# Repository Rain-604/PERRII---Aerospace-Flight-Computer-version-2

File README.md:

# PERRII – Aerospace Flight Computer version 2

## Project Overview
PERRII is a modular aerospace flight computer designed for environmental sensing and long-range data telemetry. The system is built around the ESP32-S3 Zero microcontroller and is designed to function as a scientific payload for high-altitude ballooning or atmospheric research. It integrates precision GNSS positioning, environmental gas sensing (Methane and Ammonia), and a robust power regulation system.

## My Contribution: LoRa Communication Subsystem
As the lead for the communication system, I was responsible for the hardware integration and signal integrity of the long-range telemetry link.

### Key Technical Implementations:
* **RFM98W Integration**: Integrated the RFM98W-433S2 LoRa transceiver to provide a robust, low-power, long-distance communication link between the flight computer and the ground station.
* **RF Hardware Design**: Designed the antenna interface for the AE1 Antenna, including a 100pF decoupling capacitor (C5) to ensure signal stability.
* **SPI Interface Management**: Configured the SPI bus (MOSI, MISO, SCK, NSS) to interface the RF module with the ESP32-S3, managing critical interrupt lines (DIO0-DIO5) for real-time packet handling.
* **RF Layout Optimization**: Optimized the trace routing between the RF transceiver and the antenna connector to maintain signal integrity in a compact, circular PCB form factor.

## System Architecture
While my primary focus was the communication link, I worked closely with the team to integrate the following subsystems:

### 1. Navigation & Sensing
* **GNSS Positioning**: Integration of a u-blox CAM-M8C-D GPS module for real-time tracking.
* **Environmental Monitoring**: Active monitoring of atmospheric data via SEN1 (Methane) and SEN2 (Ammonia) gas sensors.
* **Visual Telemetry**: A dedicated LED altitude output array driven by the AW9523B LED driver.

### 2. Power Management
* **Dual-Stage Regulation**: The system utilizes a high-efficiency LM2596S-5 switching buck converter for the primary 5V rail and an LM1117DT-3.3 LDO for the sensitive logic and RF rails.
* **Robust Input**: Featuring XT-30 battery connectors and reverse polarity protection via a D10 Schottky diode.

## Design Files
### 1. Schematic Design
The schematic follows a modular design separated into Power, TX, Sensor, and GPS blocks.

### 2. PCB Layout
A circular 2-layer board designed for cylindrical aerospace housing.

## Team & Credits
* **Lok Yu Lui (Rain)**: Hardware Engineer – LoRa Communication Subsystem, Power Systems, and Sensor Payloads.
* **PERRII Team**: Collaborative effort for MCU integration and software.

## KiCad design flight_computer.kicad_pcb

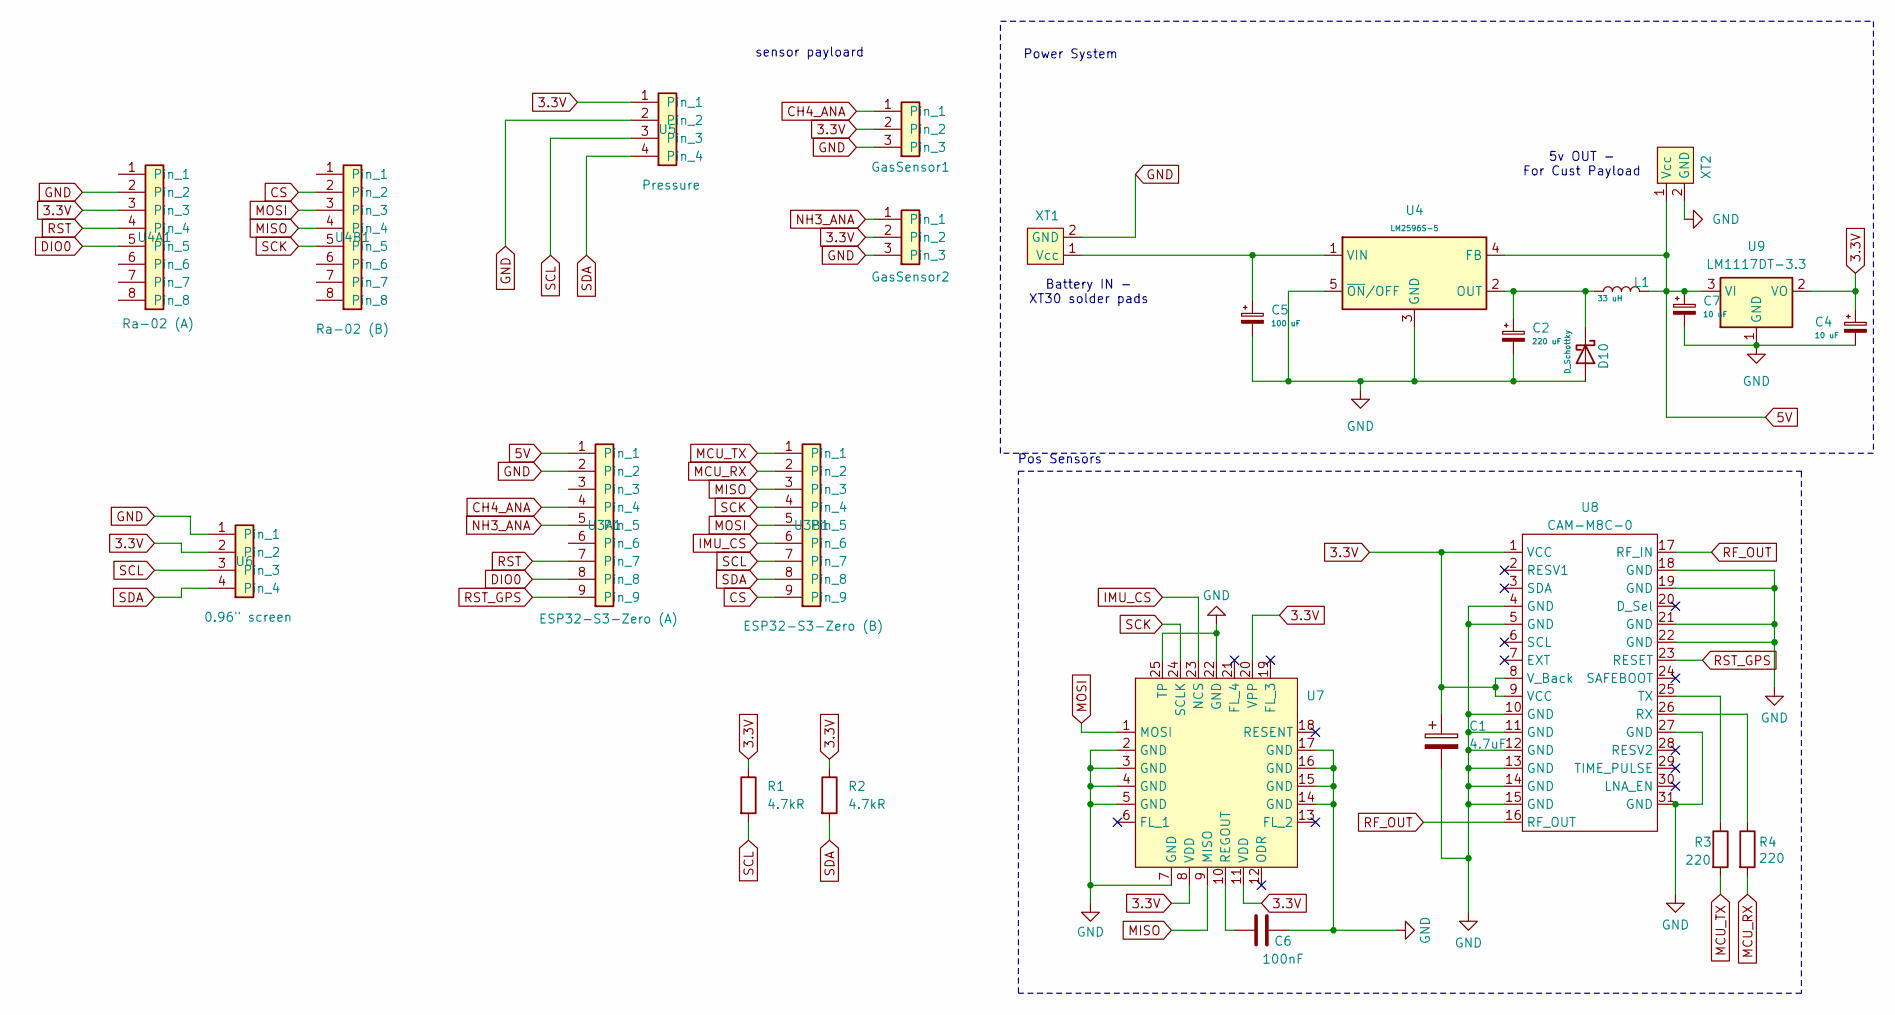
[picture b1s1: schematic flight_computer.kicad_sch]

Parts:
C1: 4.7uF; C_Disc_D3.8mm_W2.6mm_P2.50mm
C2: 220 uF; C_Disc_D3.8mm_W2.6mm_P2.50mm
C4, C7: 10 uF; C_Disc_D3.8mm_W2.6mm_P2.50mm
C5: 100 uF; C_Disc_D3.8mm_W2.6mm_P2.50mm
C6: 100nF; C_Disc_D3.8mm_W2.6mm_P2.50mm
D10: D_Schottky; D_A-405_P7.62mm_Horizontal
GasSensor1: GasSensor1; PinSocket_1x03_P2.54mm_Vertical
GasSensor2: GasSensor2; PinSocket_1x03_P2.54mm_Vertical
L1: 33 uH; L_Radial_D10.0mm_P5.00mm_Fastron_07P
R1, R2: 4.7kR; R_Axial_DIN0204_L3.6mm_D1.6mm_P7.62mm_Horizontal
R3, R4: 220; R_Axial_DIN0204_L3.6mm_D1.6mm_P7.62mm_Horizontal
U3A1: ESP32-S3-Zero (A); PinSocket_1x09_P2.54mm_Vertical
U3B1: ESP32-S3-Zero (B); PinSocket_1x09_P2.54mm_Vertical
U4: LM2596S-5; TO-263-5_TabPin3
U4A1: Ra-02 (A); PinSocket_1x08_P2.54mm_Vertical
U4B1: Ra-02 (B); PinSocket_1x08_P2.54mm_Vertical
U5: Pressure; PinSocket_1x04_P2.54mm_Vertical
U6: 0.96" screen; PinSocket_1x04_P2.54mm_Vertical
U7: QFN50P450X450X115-25N
U8: CAM-M8C-0; MODULE_CAM-M8C-0
U9: LM1117DT-3.3; TO-252-3_TabPin2
XT1: JST_XH_B2B-XH-A_1x02_P2.50mm_Vertical
XT2: AMASS_XT30UPB-F_1x02_P5.0mm_Vertical

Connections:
3.3V: C1.1, C4.1, GasSensor1.2, GasSensor2.2, R1.1, R2.1, U4A1.3, U5.1, U6.2, U7.8 (VDD), U7.11 (VDD), U7.20 (VPP), U8.1 (VCC), U8.8 (V_Back), U8.9 (VCC), U9.2 (VO)
5V: C7.1, L1.2, U3A1.1, U4.4 (FB), U9.3 (VI), XT2.1 (Vcc)
CH4_ANA: GasSensor1.1, U3A1.4
CS: U3B1.9, U4B1.2
DIO0: U3A1.8, U4A1.5
GND: C1.2, C2.2, C4.2, C5.2, C6.1, C7.2, D10.2 (A), GasSensor1.3, GasSensor2.3, U3A1.2, U4.3 (GND), U4.5 (~ON/OFF), U4A1.2, U5.2, U6.1, U7.2 (GND), U7.3 (GND), U7.4 (GND), U7.5 (GND), U7.7 (GND), U7.14 (GND), U7.15 (GND), U7.16 (GND), U7.17 (GND), U7.22 (GND), U7.25 (TP), U8.4 (GND), U8.5 (GND), U8.10 (GND), U8.11 (GND), U8.12 (GND), U8.13 (GND), U8.14 (GND), U8.15 (GND), U8.18 (GND), U8.19 (GND), U8.21 (GND), U8.22 (GND), U8.27 (GND), U8.31 (GND), U9.1 (GND), XT1.2 (GND), XT2.2 (GND)
IMU_CS: U3B1.6, U7.23 (NCS)
MCU_RX: R4.2, U3B1.2
MCU_TX: R3.2, U3B1.1
MISO: U3B1.3, U4B1.4, U7.9 (MISO)
MOSI: U3B1.5, U4B1.3, U7.1 (MOSI)
NH3_ANA: GasSensor2.1, U3A1.5
unnamed: C2.1, D10.1 (K), L1.1, U4.2 (OUT)
unnamed: C5.1, U4.1 (VIN), XT1.1 (Vcc)
unnamed: C6.2, U7.10 (REGOUT)
unnamed: R4.1, U8.26 (RX)
unnamed: R3.1, U8.25 (TX)
RF_OUT: U8.16 (RF_OUT), U8.17 (RF_IN)
RST: U3A1.7, U4A1.4
RST_GPS: U3A1.9, U8.23 (RESET)
SCK: U3B1.4, U4B1.5, U7.24 (SCLK)
SCL: R1.2, U3B1.7, U5.3, U6.3
SDA: R2.2, U3B1.8, U5.4, U6.4

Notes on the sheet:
Power System
5v OUT - For Cust Payload
sensor payloard
Pos Sensors
Battery IN - XT30 solder pads

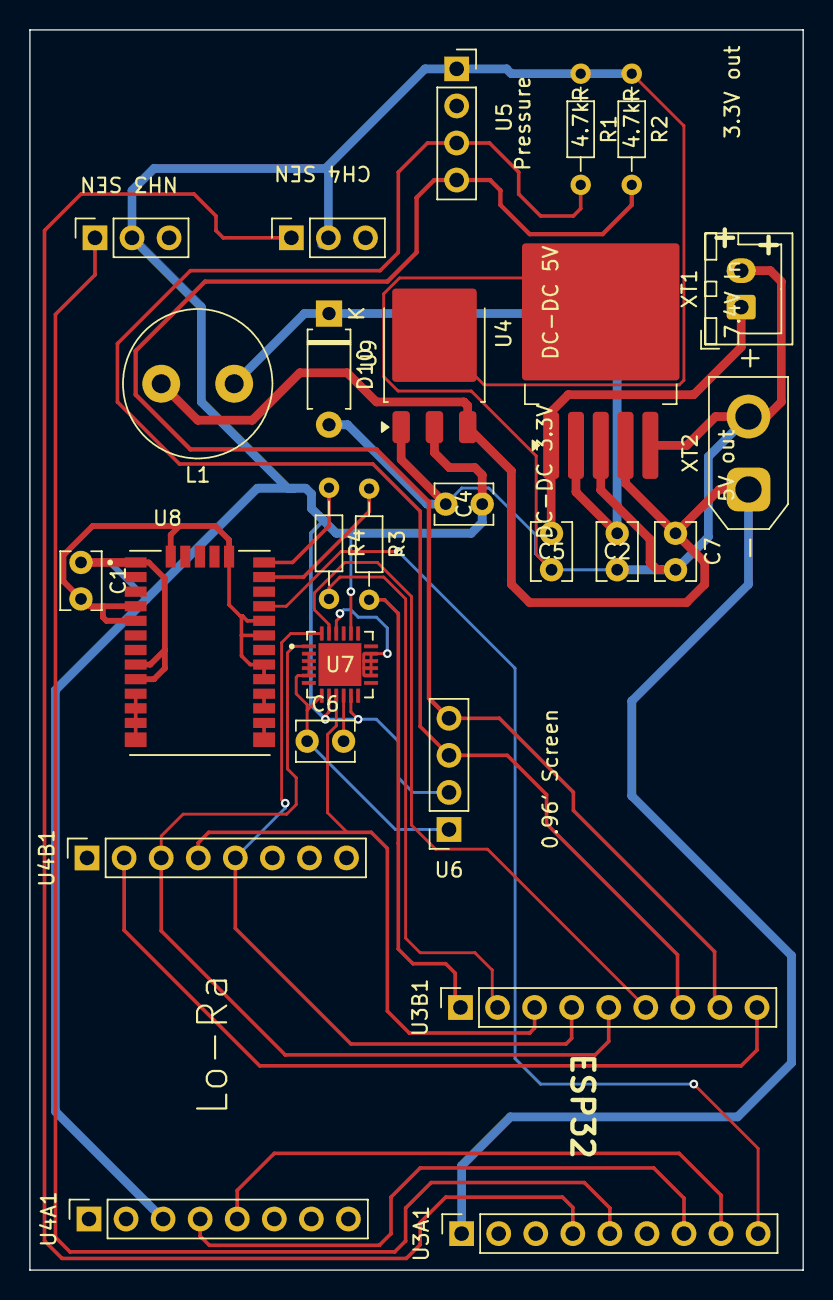
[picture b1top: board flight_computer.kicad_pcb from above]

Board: 2 copper layers, 53.0 x 85.0 mm, 30 parts (0 on the bottom side), 23 nets.

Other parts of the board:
S1: Sensor_1; PinSocket_1x02_P2.54mm_Vertical
S2: Sensor_2; PinSocket_1x02_P2.54mm_Vertical
S3: Sensor_3; PinSocket_1x02_P2.54mm_Vertical
U4A1#2: Ra-02 LoRa; PinSocket_1x08_P2.54mm_Vertical
